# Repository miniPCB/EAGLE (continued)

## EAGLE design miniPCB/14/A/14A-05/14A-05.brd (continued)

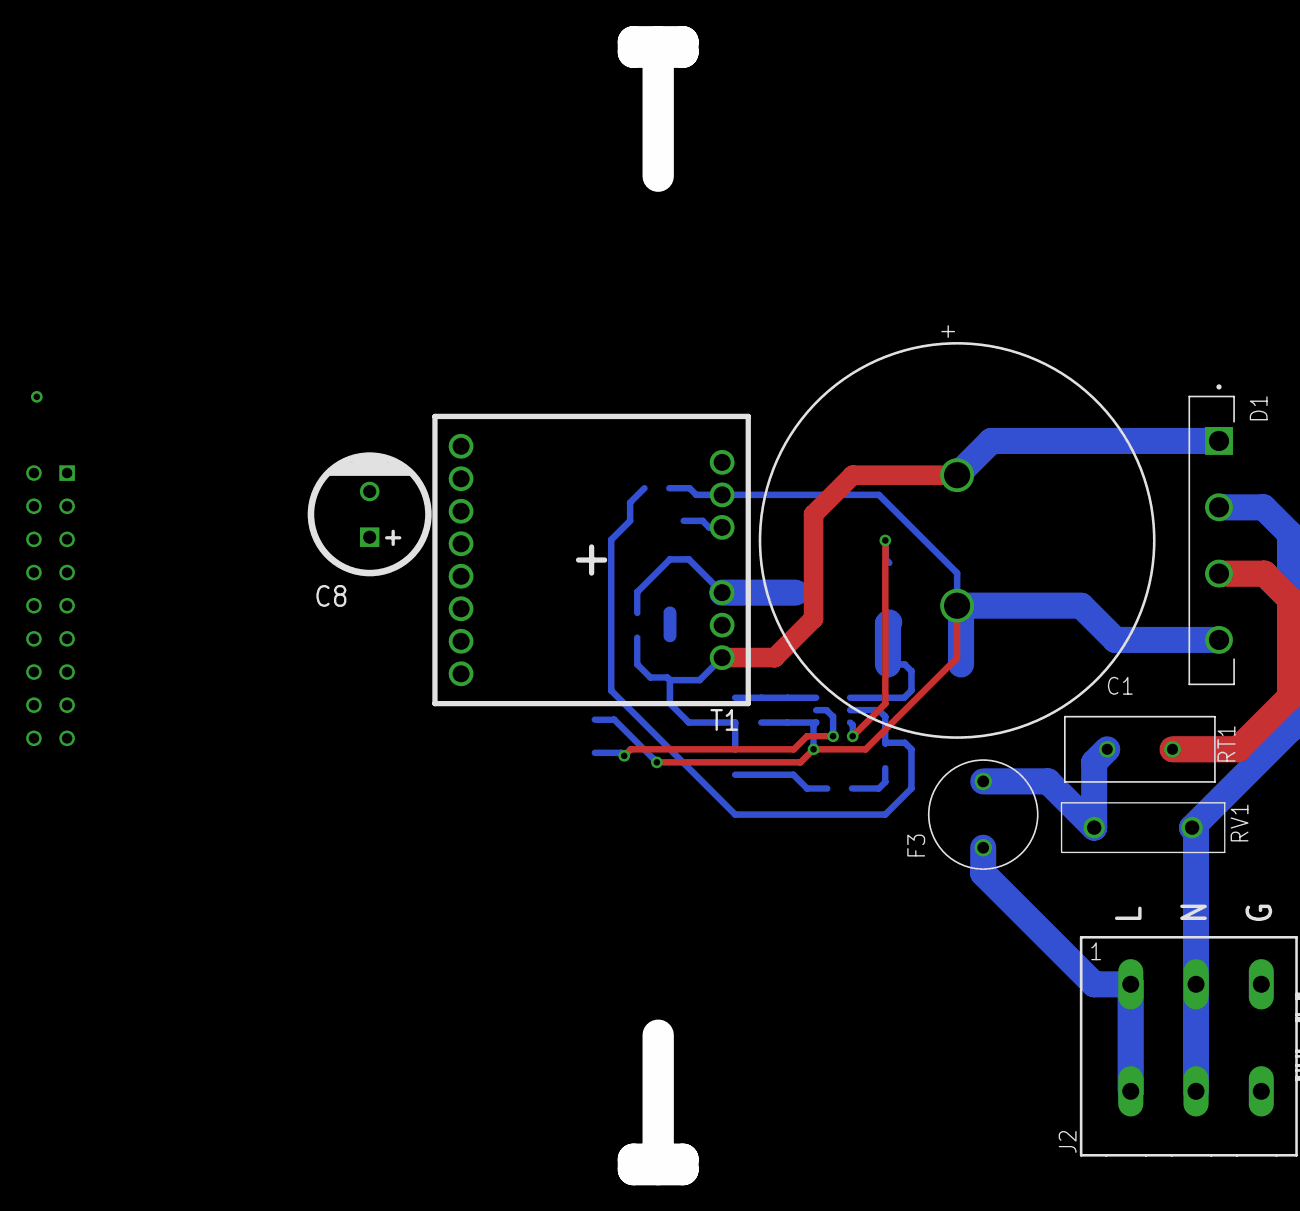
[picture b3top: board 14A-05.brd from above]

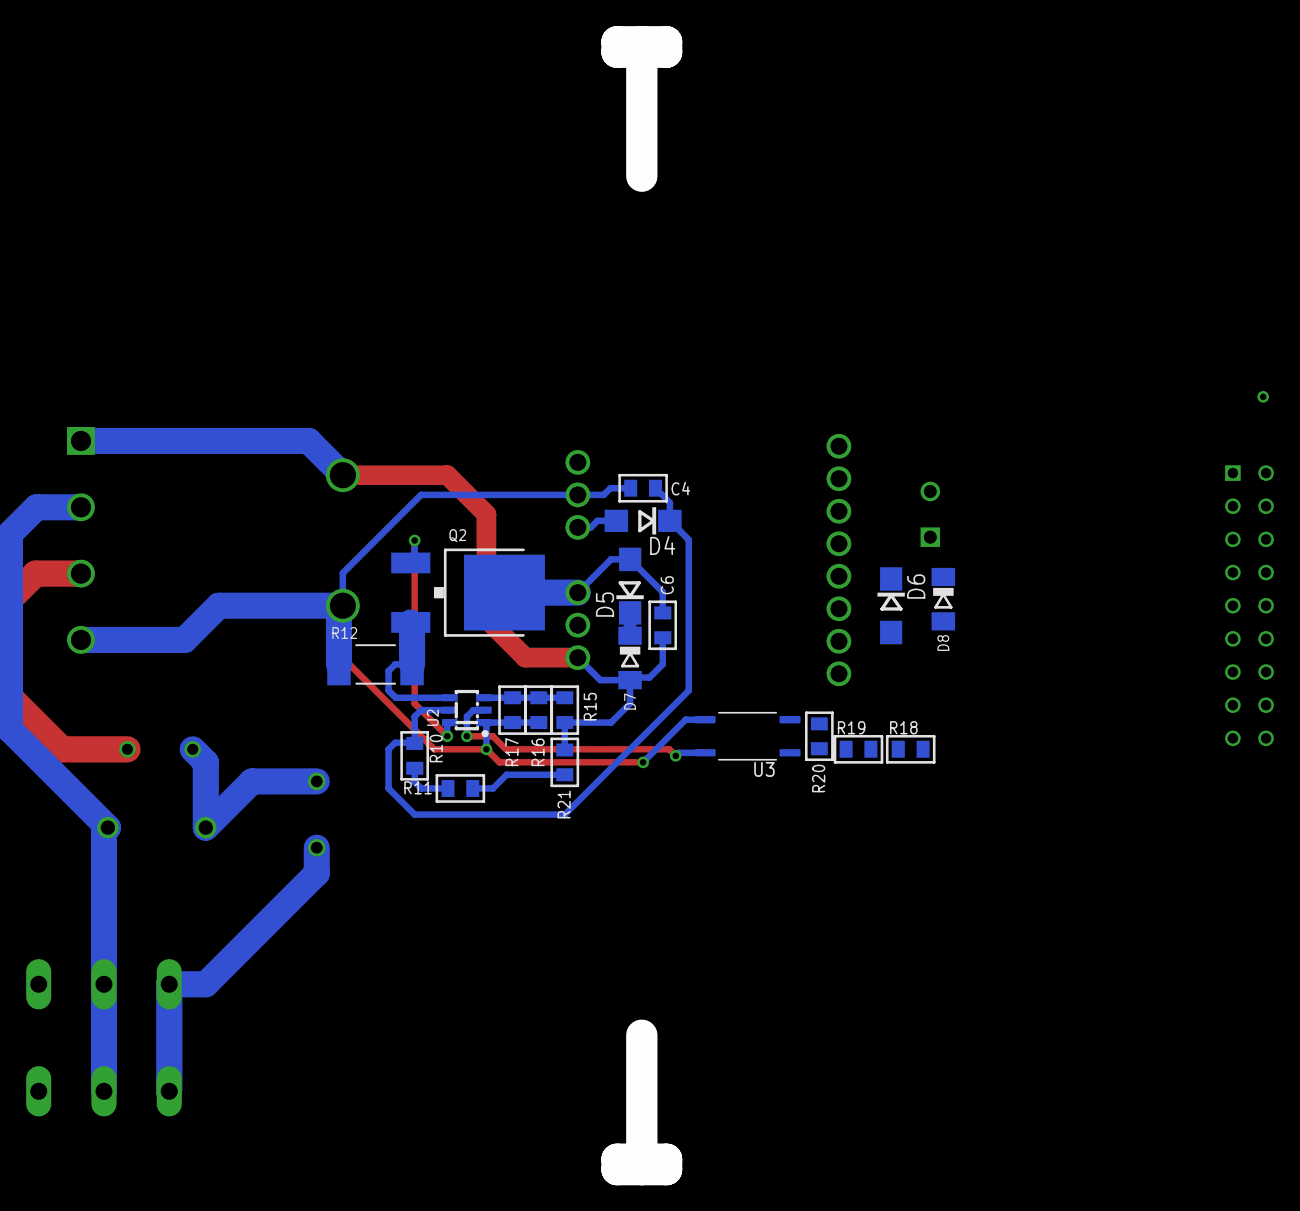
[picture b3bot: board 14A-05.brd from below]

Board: 4 copper layers, 29 parts (20 on the bottom side), 22 nets.

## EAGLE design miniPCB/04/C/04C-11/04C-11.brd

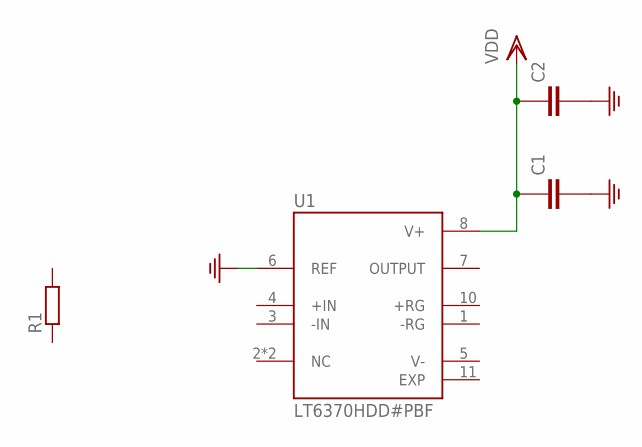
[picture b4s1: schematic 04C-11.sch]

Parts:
C1, C2: CAPACITOR0402; C0402
R1: RESISTORSMD; R0805
U1: LT6370HDD#PBF; SON50P300X300X80-11N

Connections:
GND: C1.2 (-), C2.2 (-), U1.6 (REF)
V-: U1.5 (V-)
VDD: C1.1 (+), C2.1 (+), U1.8 (V+)

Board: 2 copper layers, 4 parts (0 on the bottom side), 2 nets, no tracks yet.

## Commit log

2022-11-11 Test
2022-11-11 Thumbnails and Document Templates
2022-11-11 11NOV2022
2022-11-22 NM.21NOV2022
2022-12-01 NM.30NOV2022(1)
2022-12-01 NM.01DEC2022
2022-12-02 NM.01DEC2022(2)
2022-12-09 NM.08DEC2022
2023-01-09 NM.08JAN2023
2023-01-15 NM.14JAN2023
2023-01-15 NM.15JAN2023
2023-01-16 NM.16JAN2023
2023-01-17 NM.17JAN2023
2023-01-18 NM.18JAN2023
2023-01-28 NM.28JAN2023
2023-01-31 NM.30JAN2023
2023-02-01 NM.31JAN2023
2023-02-02 NM.01FEB2023
2023-02-03 NM.02FEB2023
2023-02-03 NM.03FEB2023
2023-02-04 NM.04FEB2023
2023-02-05 NM.05FEB2023
2023-02-24 NM.24FEB2023
2023-02-28 NM.28FEB2023
2023-03-05 NM.05MAR2023
2023-03-10 NM.09MAR2023
2023-03-11 NM.11MAR2023
2023-03-12 NM.12MAR2023
2023-04-01 NM.01APR2023
2023-04-03 NM.02APR2023
2023-07-09 NM.08JUL2023
2023-07-18 NM.17JUL2023
2023-07-19 NM.18JUL2023
2023-07-28 NM.28JUL2023
2023-08-09 NM.09AUG2023
2023-09-03 NM.03SEP2023
2023-09-08 NM.07SEP2023
2023-09-15 NM.15SEP2023
2023-09-22 NM.21SEP2023
2023-10-03 NM.03OCT2023
2023-10-04 NM.04OCT2023
2023-10-24 NM.23OCT2023
2023-10-25 NM.25OCT2023
2023-10-26 NM.26OCT2023
2023-10-27 NM.27OCT2023
2023-10-29 NM.29OCT2023
2023-11-04 NM.04NOV2023
2023-11-08 NM.08NOV2023
2023-11-09 NM.09NOV2023
2023-11-10 NM.10NOV2023
2023-11-12 NM.12NOV2023
2023-11-23 NM.23NOV2023
2023-11-27 NM.27NOV2023
2024-03-07 NM.07MAR2024
2024-04-05 Attempting to fix my Git merge error.
2024-04-06 NM.06APR2024
2024-04-22 NM.21APR2024
2024-04-23 NM.22APR2024
2024-04-27 NM.26APR2024
2024-05-03 NM.02MAY2024
2024-07-09 NM.09JUL2024
2024-07-10 NM.10JUL2024
2024-07-13 NM.13JUL2024
2024-11-16 BC Housing Boards
2024-11-17 Giving vScore boards regular part numbers
2024-11-17 Probe boards, KE6060
2024-11-18 PROBE BOARD, BNC, 2CH
2024-11-23 NM.23NOV2024
2024-11-27 NM.26NOV2024
2024-11-27 NM.27NOV2024
